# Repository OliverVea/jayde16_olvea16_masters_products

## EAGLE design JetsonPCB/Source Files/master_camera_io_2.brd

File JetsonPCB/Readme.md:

- Source Files

Contains the source files for the schematics, board layouts and the overview.

- JetsonPrintOverview

Illustrates GPIO port mappings to pins in the schematics.

- connector_board.pdf

Board layout of the connector board, used to connect the Jetson to the IO board.

- connector_schematic.pdf

Schematic of the connector board, used to connect the Jetson to the IO board.

- io_board.pdf

Board layout of the io board, used to connect the Jetson to buttons and LEDs.

- io_schematic.pdf

Schematic of the io board, used to connect the Jetson to buttons and LEDs.

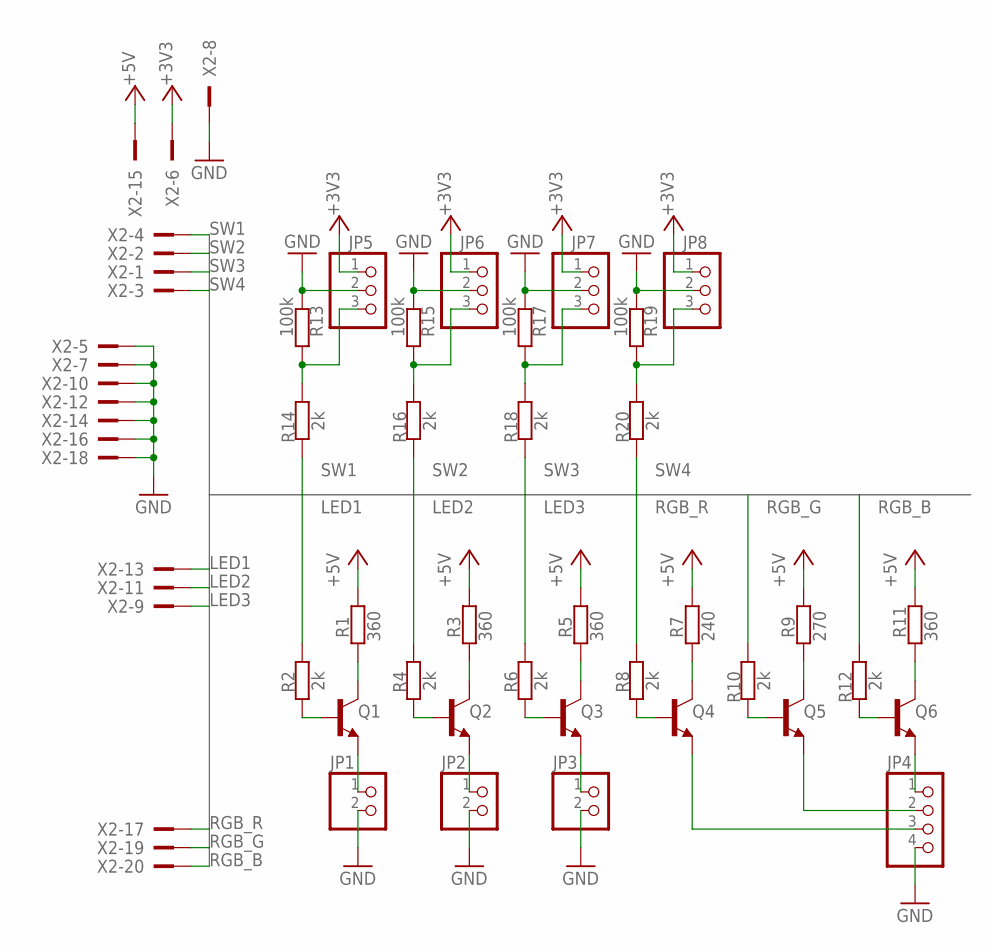
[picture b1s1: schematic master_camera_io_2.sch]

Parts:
JP1, JP2, JP3: PINHD-1X2; 1X02
JP4: PINHD-1X4; 1X04
JP5, JP6, JP7, JP8: PINHD-1X3; 1X03
Q1, Q2, Q3, Q4, Q5, Q6: BC850SMD; SOT23-BEC
R1, R3, R5, R11: 360; R0805
R2, R4, R6, R8, R10, R12, R14, R16, R18, R20: 2k; R0805
R7: 240; R0805
R9: 270; R0805
R13, R15, R17, R19: 100k; R0805
X2: 2520-; PAK100/2500-20

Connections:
+3V3: JP5.1, JP6.1, JP7.1, JP8.1, X2.6
+5V: R1.2, R3.2, R5.2, R7.2, R9.2, R11.2, X2.15
GND: JP1.2, JP2.2, JP3.2, JP4.4, JP5.2, JP6.2, JP7.2, JP8.2, R13.2, R15.2, R17.2, R19.2, X2.5, X2.7, X2.8, X2.10, X2.12, X2.14, X2.16, X2.18
LED1: R2.1, X2.13
LED2: R4.1, X2.11
LED3: R6.1, X2.9
unnamed: JP1.1, Q1.E
unnamed: Q1.B, R2.2
unnamed: Q1.C, R1.1
unnamed: JP2.1, Q2.E
unnamed: Q2.B, R4.2
unnamed: Q2.C, R3.1
unnamed: JP3.1, Q3.E
unnamed: Q3.B, R6.2
unnamed: Q3.C, R5.1
unnamed: JP4.1, Q6.E
unnamed: Q4.B, R8.2
unnamed: Q4.C, R7.1
unnamed: JP4.2, Q5.E
unnamed: Q5.B, R10.2
unnamed: Q5.C, R9.1
unnamed: JP4.3, Q4.E
unnamed: Q6.B, R12.2
unnamed: Q6.C, R11.1
unnamed: JP5.3, R13.1, R14.1
unnamed: JP6.3, R15.1, R16.1
unnamed: JP7.3, R17.1, R18.1
unnamed: JP8.3, R19.1, R20.1
RGB_B: R12.1, X2.20
RGB_G: R10.1, X2.19
RGB_R: R8.1, X2.17
SW1: R14.2, X2.4
SW2: R16.2, X2.2
SW3: R18.2, X2.1
SW4: R20.2, X2.3

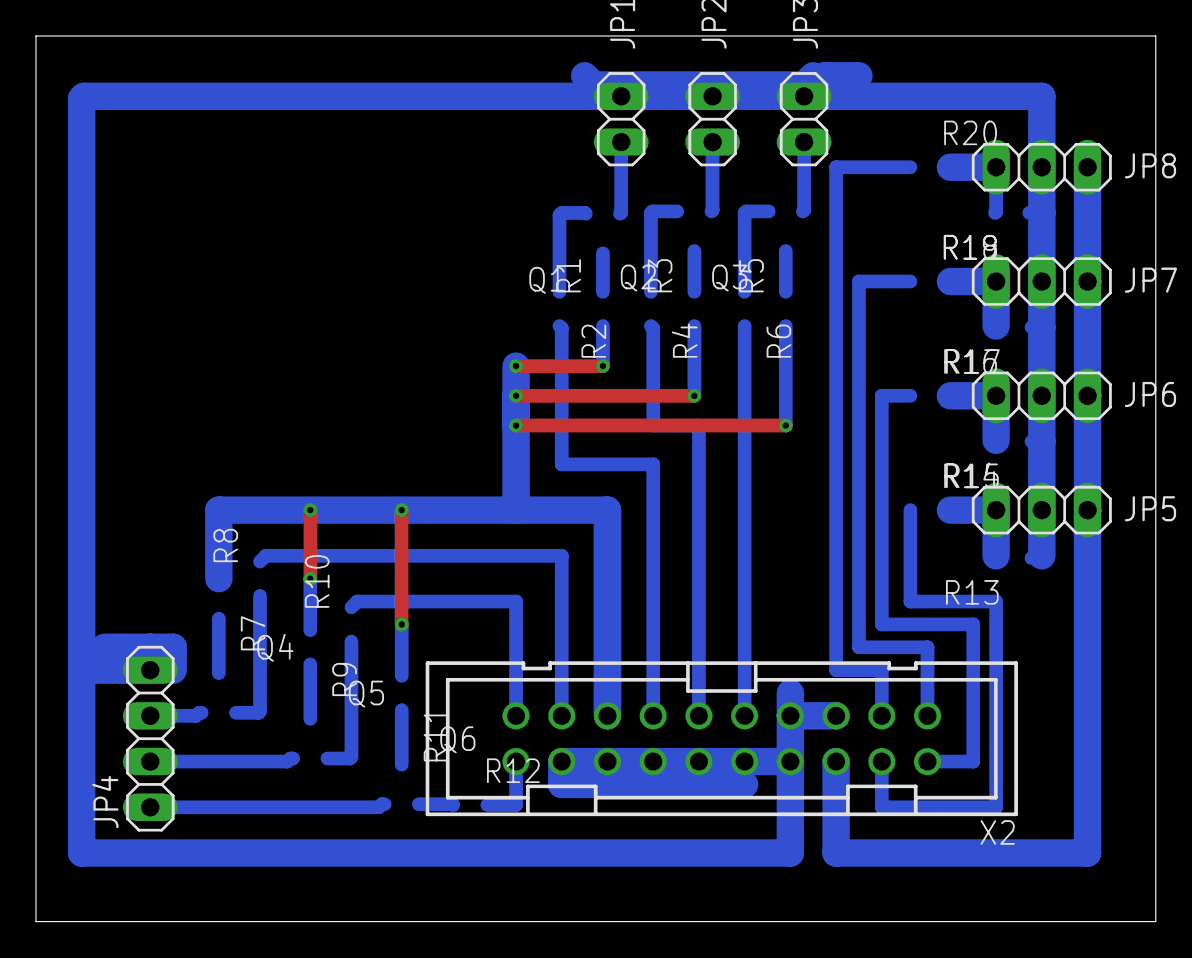
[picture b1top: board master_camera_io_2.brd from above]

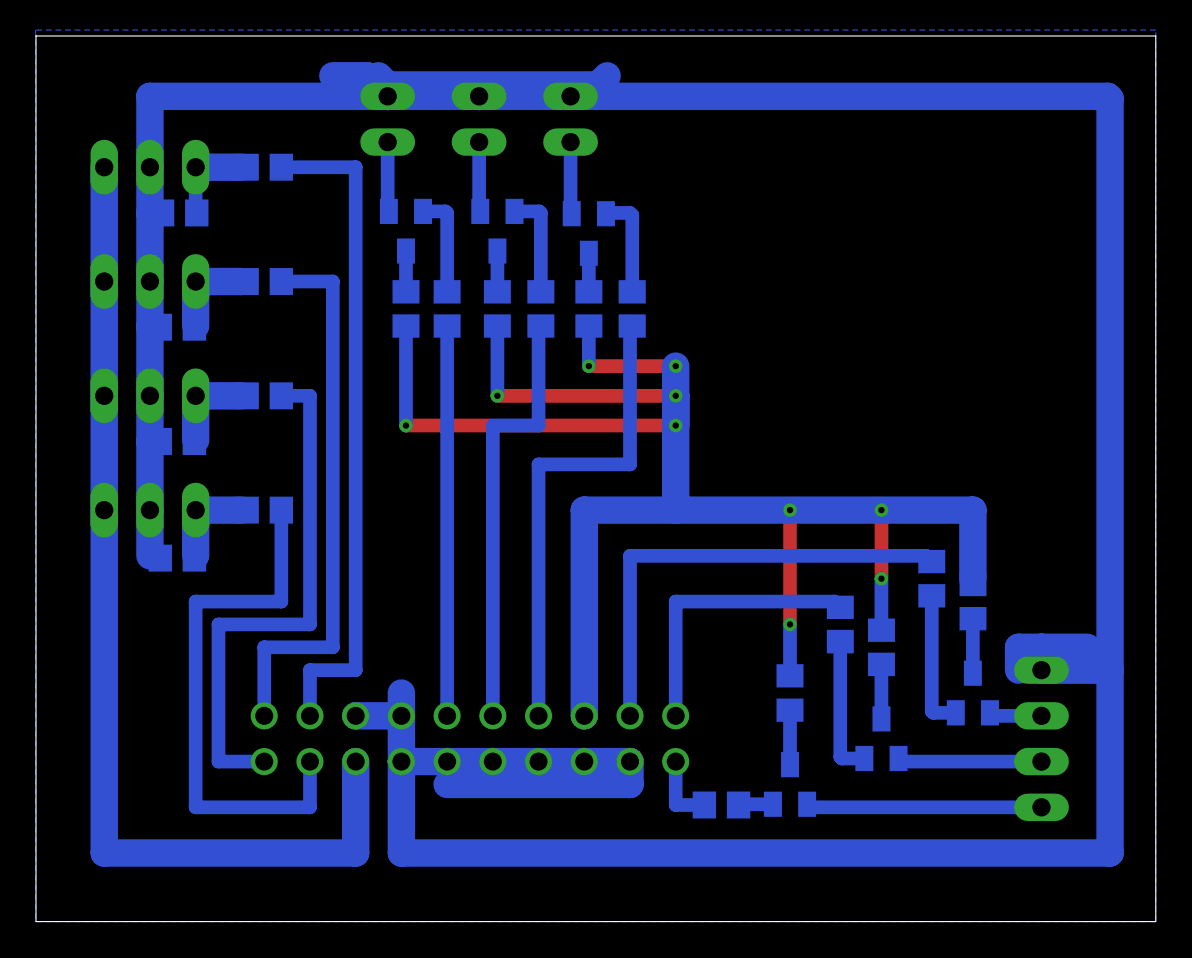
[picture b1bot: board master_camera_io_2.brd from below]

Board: 2 copper layers, 62.2 x 49.2 mm, 35 parts (26 on the bottom side), 35 nets.

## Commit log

2021-03-19 Java push
2021-05-09 Calib initialization
2021-05-09 adsads
2021-05-09 sdsa
2021-05-18 JetsonCamera
2021-05-18 JetsonSchematics
2021-05-21 Codebook stuff
2021-05-24 SLAMSandbox
2021-05-31 Gis og SLAM Simulering
2021-05-31 Removal of pycache files and folders
2021-05-31 Slam reordering
2021-05-31 Read files and updated readme
2021-06-01 vo_ir_od
2021-06-01 readmes
